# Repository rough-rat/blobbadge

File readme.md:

# Blobbadge

This is a backlight badge. It charlieplexes LEDs with PY32F002.

## IRL

The prototype front has been made as green, to speed up / optimize the development.

Proof of concept firmware, freshly rewritten in rust

https://github.com/rough-rat/blobbadge-rs

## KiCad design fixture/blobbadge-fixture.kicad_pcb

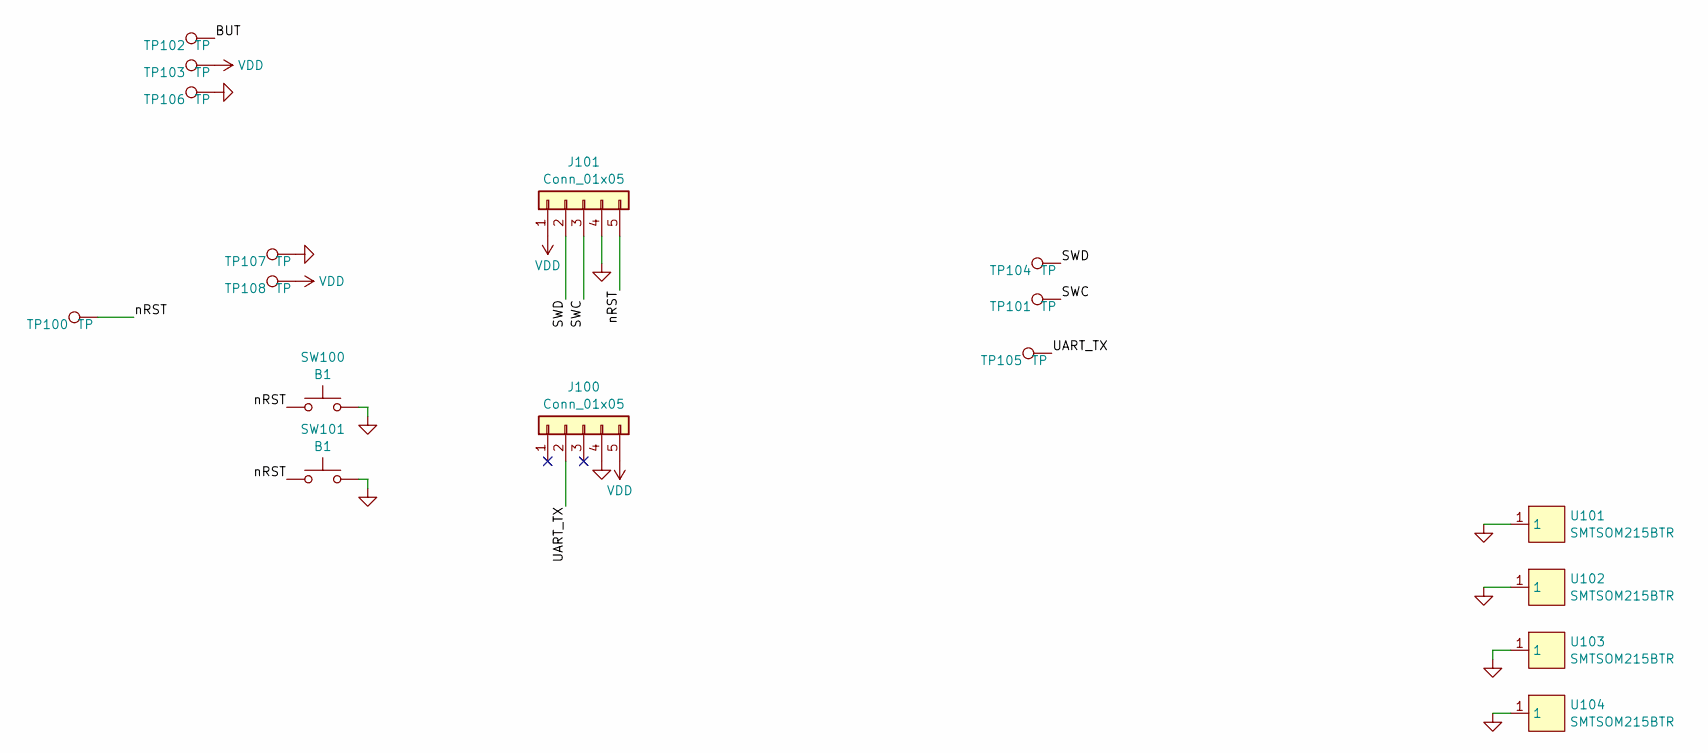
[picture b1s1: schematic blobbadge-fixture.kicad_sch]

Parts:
J100, J101: Conn_01x05; PinHeader_1x05_P2.54mm_SMD_flat
SW100, SW101: B1; SW_SPST_FSMSM; LCSC DNP
TP100, TP101, TP102, TP103, TP104, TP105, TP106, TP107, TP108: TP; TestPoint_THTPad_D4.0mm_Drill2.0mm; LCSC DNP
U101, U102, U103, U104: SMTSOM215BTR; SMD_BD5.6-D3.6; LCSC C5301777

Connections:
/BUT: TP102.1
/SWC: J101.3, TP101.1
/SWD: J101.2, TP104.1
/UART_TX: J100.2, TP105.1
/nRST: J101.5, SW100.1, SW101.1, TP100.1
GND: J100.4, J101.4, SW100.2, SW101.2, TP106.1, TP107.1, U101.1, U102.1, U103.1, U104.1
VDD: J100.5, J101.1, TP103.1, TP108.1

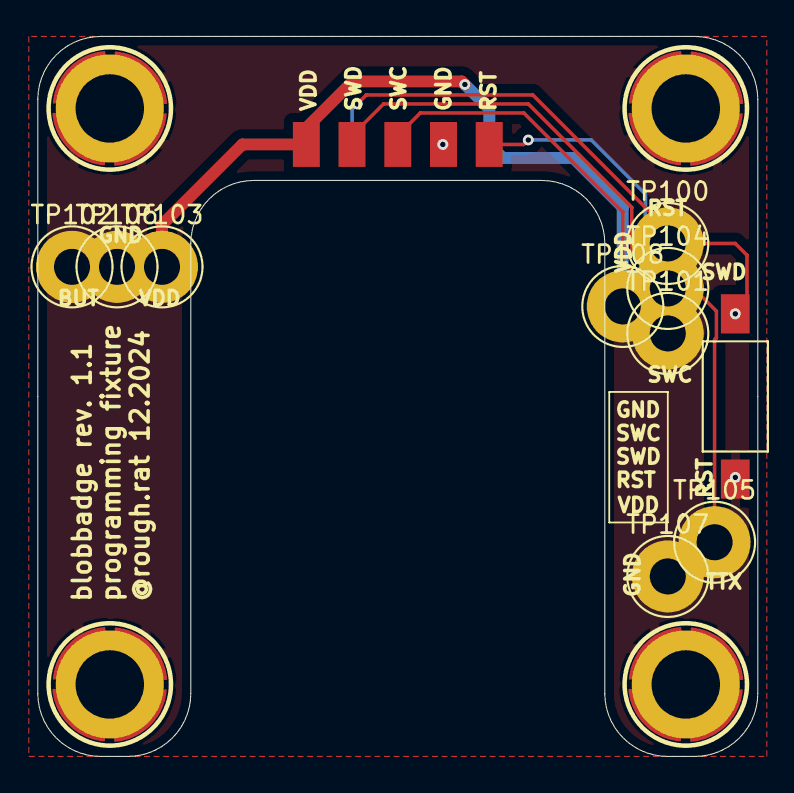
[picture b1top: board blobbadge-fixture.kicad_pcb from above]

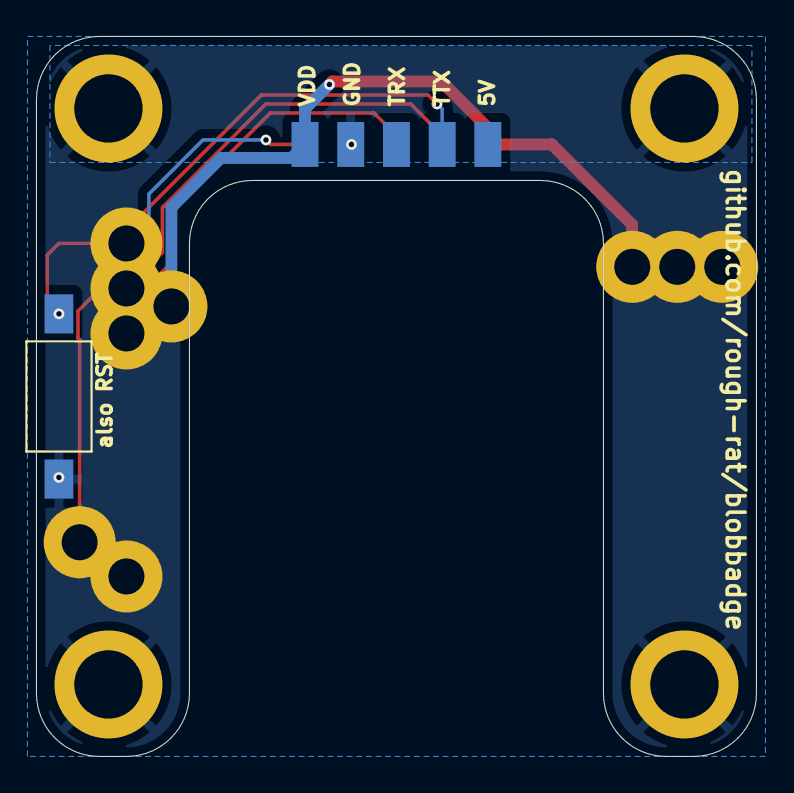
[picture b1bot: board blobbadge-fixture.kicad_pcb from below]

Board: 2 copper layers, 40.0 x 40.0 mm, 17 parts (2 on the bottom side), 6 nets.

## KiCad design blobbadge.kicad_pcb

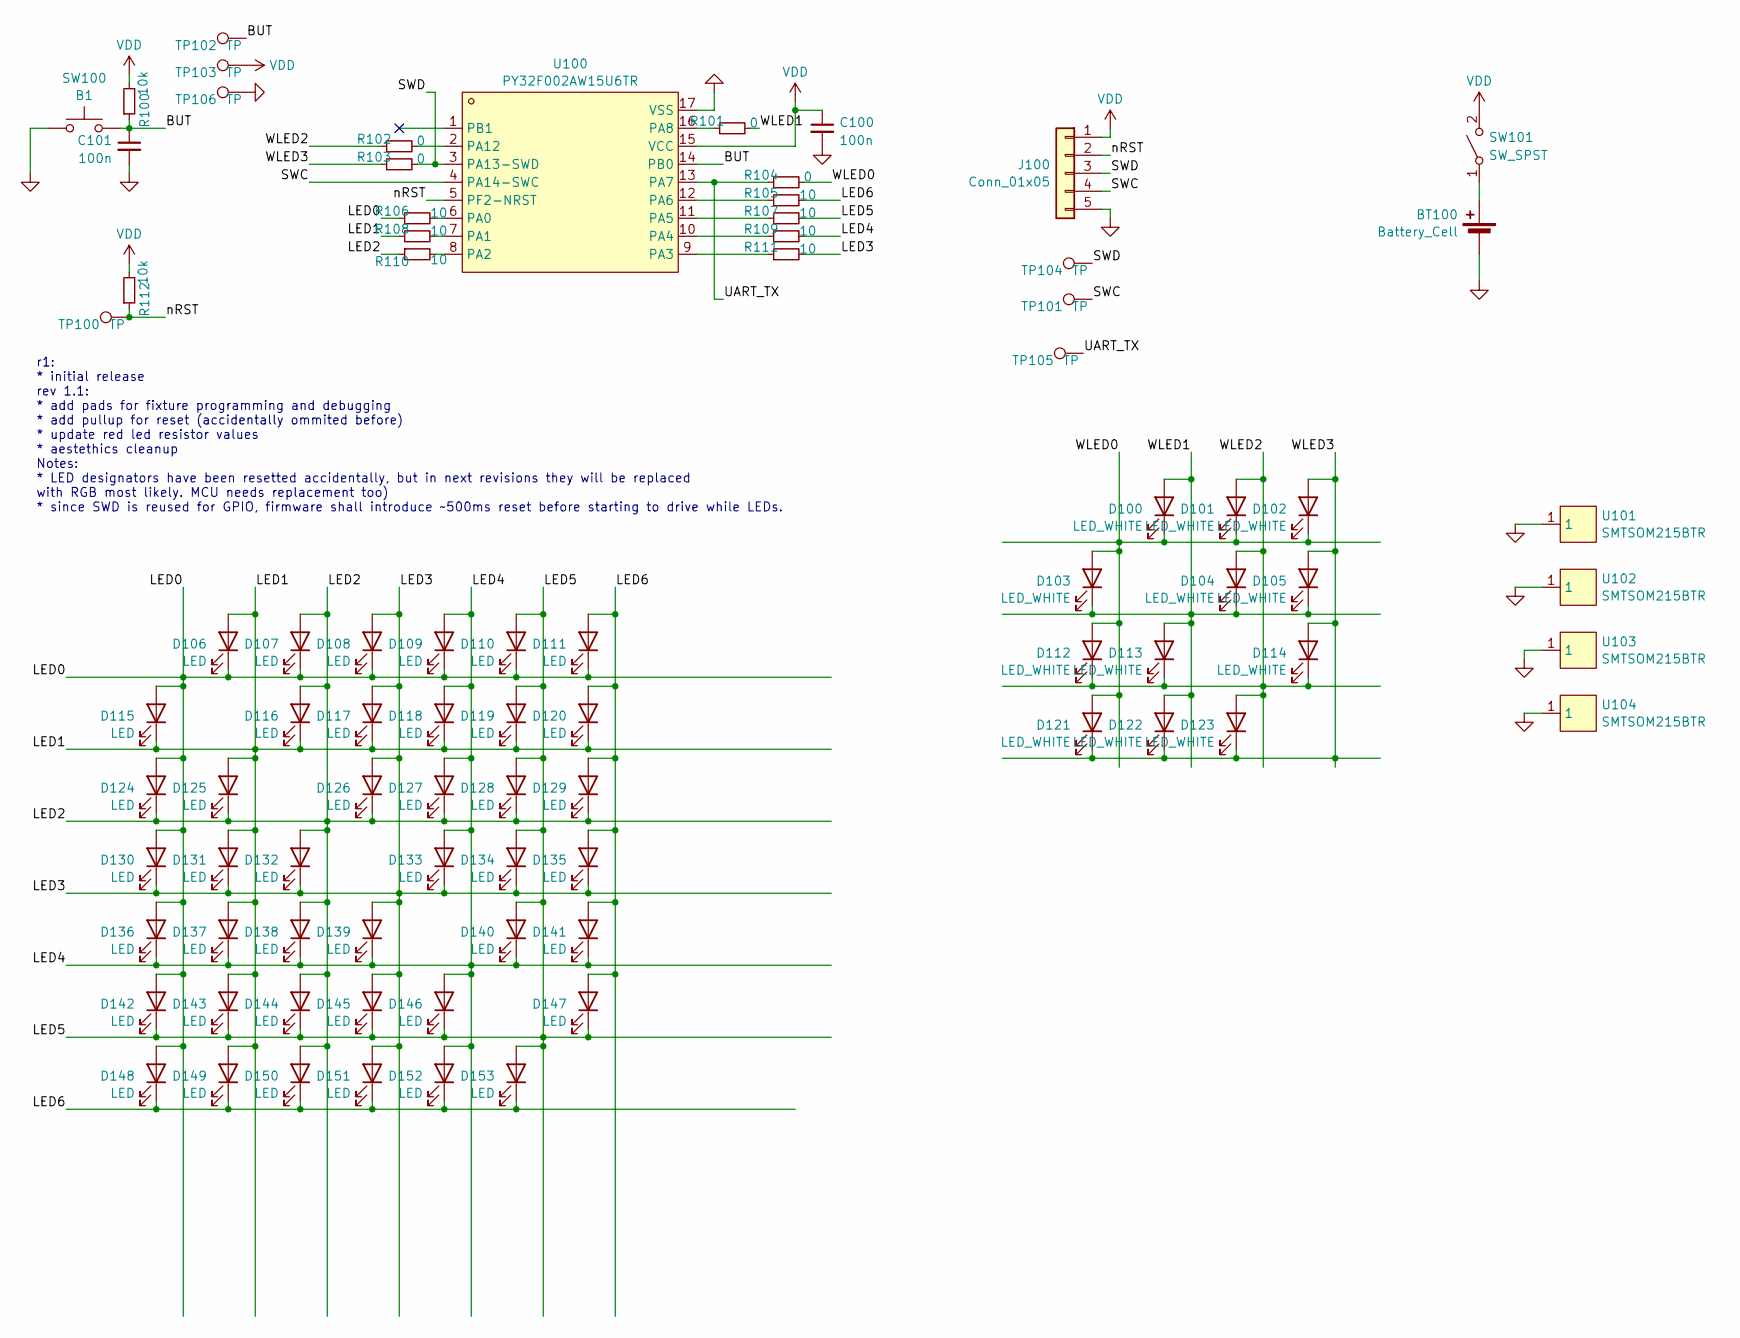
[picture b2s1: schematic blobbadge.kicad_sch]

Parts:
BT100: Battery_Cell; BatteryHolder_Keystone_1060_1x2032; LCSC DNP
C100, C101: 100n; C_0402_1005Metric; LCSC C1525
D100, D101, D102, D103, D104, D105, D112, D113, D114, D121, D122, D123: LED_WHITE; LED_0603_1608Metric; LCSC C34499
D106, D107, D108, D109, D110, D111, D115, D116, D117, D118, D119, D120, D124, D125, D126, D127, D128, D129, D130, D131, D132, D133, D134, D135, D136, D137, D138, D139, D140, D141, D142, D143, D144, D145, D146, D147, D148, D149, D150, D151, D152, D153: LED; LED_0805_2012Metric; LCSC C84256
J100: Conn_01x05; PinHeader_1x05_P1.27mm_Vertical; LCSC DNP
R100, R112: 10k; R_0402_1005Metric; LCSC C25744
R101, R102, R103, R104: 0; R_0603_1608Metric; LCSC C21189
R105, R106, R107, R108, R109, R110, R111: 10; R_0603_1608Metric; LCSC C22859
SW100: B1; SW_SPST_FSMSM; LCSC DNP
SW101: SW_SPST; flashlightButton; LCSC DNP
TP100, TP101, TP102, TP103, TP104, TP105, TP106: TP; TestPoint_Pad_D1.0mm; LCSC DNP
U100: PY32F002AW15U6TR; TQFN-16_L3.0-W3.0-P0.50-BL-EP1.7; LCSC C5291740
U101, U102, U103, U104: SMTSOM215BTR; SMD_BD5.6-D3.6; LCSC C5301777

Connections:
/BUT: C101.1, R100.1, SW100.2, TP102.1, U100.14 (PB0)
/LED0: D106.1 (K), D107.1 (K), D108.1 (K), D109.1 (K), D110.1 (K), D111.1 (K), D115.2 (A), D124.2 (A), D130.2 (A), D136.2 (A), D142.2 (A), D148.2 (A), R106.1
/LED1: D106.2 (A), D115.1 (K), D116.1 (K), D117.1 (K), D118.1 (K), D119.1 (K), D120.1 (K), D125.2 (A), D131.2 (A), D137.2 (A), D143.2 (A), D149.2 (A), R108.1
/LED2: D107.2 (A), D116.2 (A), D124.1 (K), D125.1 (K), D126.1 (K), D127.1 (K), D128.1 (K), D129.1 (K), D132.2 (A), D138.2 (A), D144.2 (A), D150.2 (A), R110.1
/LED3: D108.2 (A), D117.2 (A), D126.2 (A), D130.1 (K), D131.1 (K), D132.1 (K), D133.1 (K), D134.1 (K), D135.1 (K), D139.2 (A), D145.2 (A), D151.2 (A), R111.2
/LED4: D109.2 (A), D118.2 (A), D127.2 (A), D133.2 (A), D136.1 (K), D137.1 (K), D138.1 (K), D139.1 (K), D140.1 (K), D141.1 (K), D146.2 (A), D152.2 (A), R109.2
/LED5: D110.2 (A), D119.2 (A), D128.2 (A), D134.2 (A), D140.2 (A), D142.1 (K), D143.1 (K), D144.1 (K), D145.1 (K), D146.1 (K), D147.1 (K), D153.2 (A), R107.2
/LED6: D111.2 (A), D120.2 (A), D129.2 (A), D135.2 (A), D141.2 (A), D147.2 (A), D148.1 (K), D149.1 (K), D150.1 (K), D151.1 (K), D152.1 (K), D153.1 (K), R105.2
/SWC: J100.4, TP101.1, U100.4 (PA14-SWC)
/SWD: J100.3, R103.2, TP104.1, U100.3 (PA13-SWD)
/UART_TX: R104.1, TP105.1, U100.13 (PA7)
/WLED0: D100.1 (K), D101.1 (K), D102.1 (K), D103.2 (A), D112.2 (A), D121.2 (A), R104.2
/WLED1: D100.2 (A), D103.1 (K), D104.1 (K), D105.1 (K), D113.2 (A), D122.2 (A), R101.2
/WLED2: D101.2 (A), D104.2 (A), D112.1 (K), D113.1 (K), D114.1 (K), D123.2 (A), R102.1
/WLED3: D102.2 (A), D105.2 (A), D114.2 (A), D121.1 (K), D122.1 (K), D123.1 (K), R103.1
/nRST: J100.2, R112.1, TP100.1, U100.5 (PF2-NRST)
GND: BT100.2 (-), C100.2, C101.2, J100.5, SW100.1, TP106.1, U100.17 (VSS), U101.1, U102.1, U103.1, U104.1
unnamed: BT100.1 (+), SW101.1 (A)
unnamed: R106.2, U100.6 (PA0)
unnamed: R108.2, U100.7 (PA1)
unnamed: R110.2, U100.8 (PA2)
unnamed: R111.1, U100.9 (PA3)
unnamed: R109.1, U100.10 (PA4)
unnamed: R107.1, U100.11 (PA5)
unnamed: R105.1, U100.12 (PA6)
unnamed: R101.1, U100.16 (PA8)
unnamed: R102.2, U100.2 (PA12)
VDD: C100.1, J100.1, R100.2, R112.2, SW101.2 (B), TP103.1, U100.15 (VCC)

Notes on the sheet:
r1: * initial release rev 1.1: * add pads for fixture programming and debugging * add pullup for reset (accidentally ommited before) * update red led resistor values * aestethics cleanup Notes: * LED designators have been resetted accidentally, but in next revisions they will be replaced with RGB m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

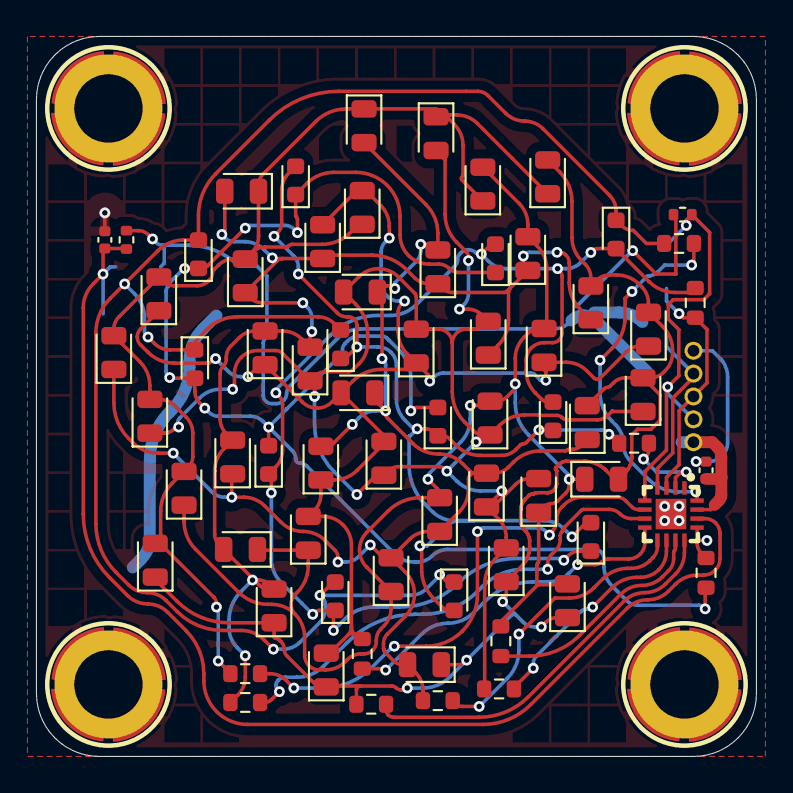
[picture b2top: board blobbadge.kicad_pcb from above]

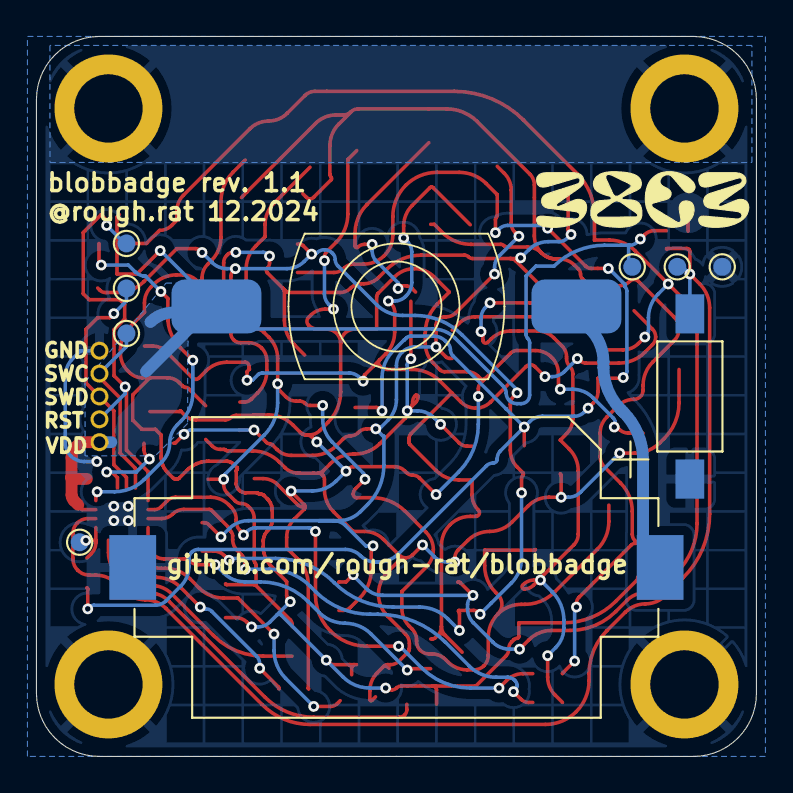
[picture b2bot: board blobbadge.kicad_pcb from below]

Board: 2 copper layers, 40.0 x 40.0 mm, 85 parts (10 on the bottom side), 28 nets.

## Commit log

2024-11-23 Add files
2024-11-24 before charlieplex remake
2024-11-24 add white leds, and stuff
2024-11-25 weaseleds
2024-11-25 start route
2024-11-25 pre_melt
2024-11-25 finish route
2024-11-26 add order pcb and stuff
2024-12-02 cleanup, add nice things
2024-12-02 add front
2024-12-07 add r1 order, prepare rev1.1 order
2024-12-15 add 2nd order and some updates
2024-12-15 add support pcbs
2024-12-15 add more description
